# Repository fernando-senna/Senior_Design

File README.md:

# Senior_Design
Eye Tracker - Senior Design Project
As the name suggests this is a Systems Design project. Our goal is to design and develop an affordable, sleek and accurate eye tracking system. This project contains the entire documentation and code. 
                    # Last Updated: Oct 31, 2015

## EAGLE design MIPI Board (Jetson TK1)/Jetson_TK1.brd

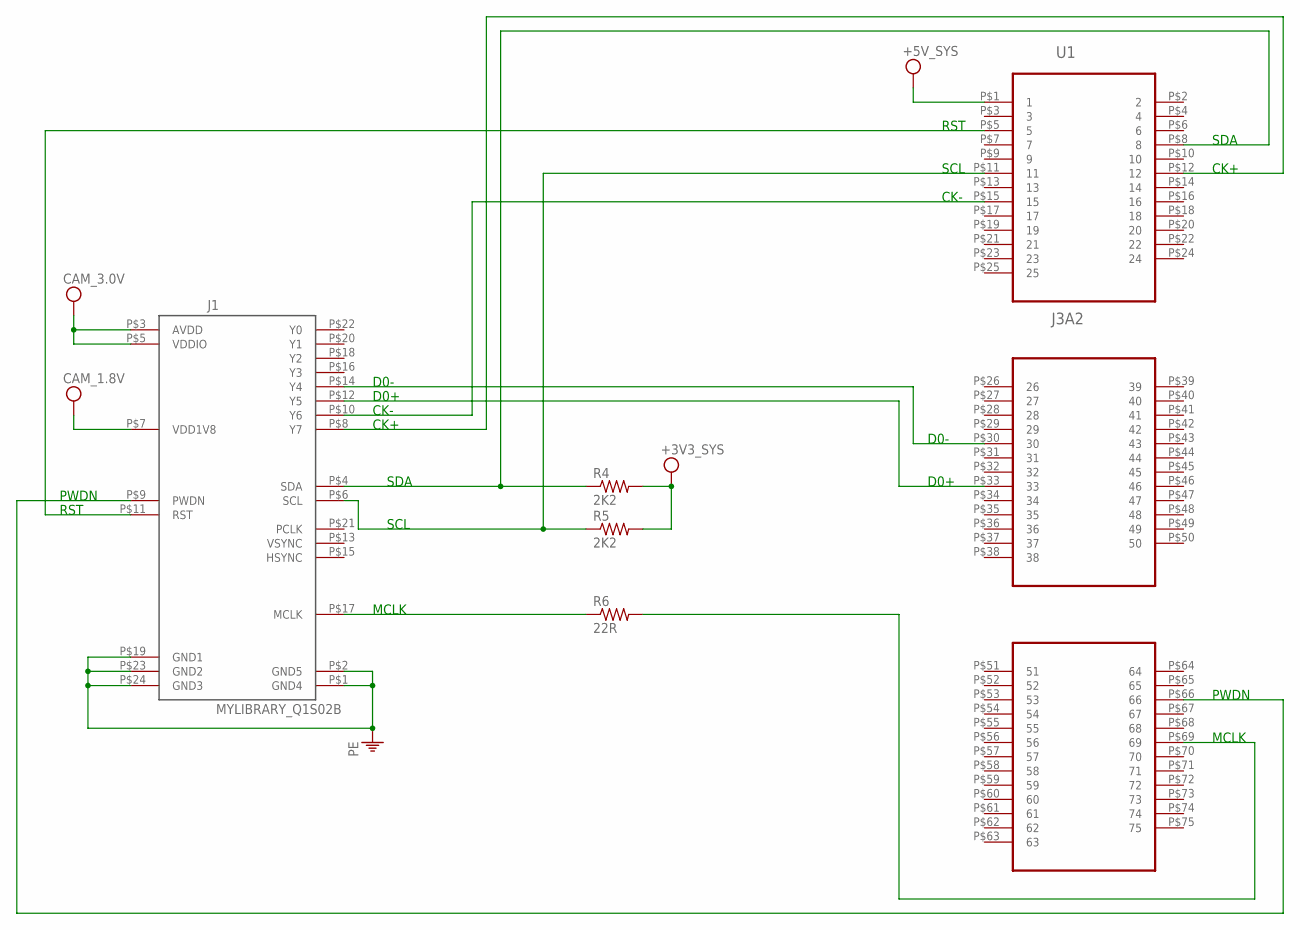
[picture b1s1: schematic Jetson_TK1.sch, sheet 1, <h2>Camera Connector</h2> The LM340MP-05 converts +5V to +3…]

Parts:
J1: MYLIBRARY_Q1S02B; MYLIBRARY_AXK824145WG
R4, R5: 2K2; R0603
R6: 22R; R0603
U1: J3A2; SQW-150-01-F-T

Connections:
unnamed: J1.P$8 (Y7), U1.P$12 (12)
unnamed: J1.P$4 (SDA), R4.1, U1.P$8 (8)
unnamed: J1.P$6 (SCL), R5.1, U1.P$11 (11)
unnamed: J1.P$10 (Y6), U1.P$15 (15)
unnamed: J1.P$12 (Y5), U1.P$33 (33)
unnamed: J1.P$14 (Y4), U1.P$30 (30)
unnamed: J1.P$17 (MCLK), R6.1
unnamed: R6.2, U1.P$69 (69)
unnamed: J1.P$11 (RST), U1.P$5 (5)
unnamed: J1.P$9 (PWDN), U1.P$66 (66)
PE: J1.P$1 (GND4), J1.P$2 (GND5), J1.P$19 (GND1), J1.P$23 (GND2), J1.P$24 (GND3); also elsewhere on the board
VDD: J1.P$3 (AVDD), J1.P$5 (VDDIO), J1.P$7 (VDD1V8), R4.2, R5.2, U1.P$1 (1); also elsewhere on the board

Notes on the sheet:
SDA
SCL
CK+
CK-
D0+
D0-
MCLK
RST
PWDN

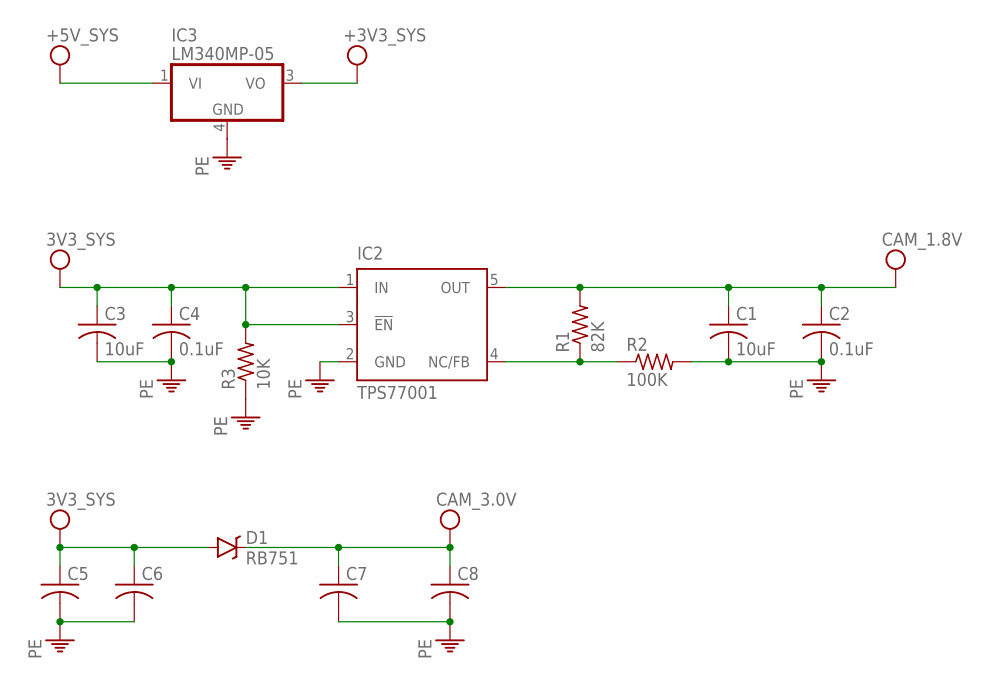
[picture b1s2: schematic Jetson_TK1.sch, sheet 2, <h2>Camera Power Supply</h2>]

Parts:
C1, C3: 10uF; C0603
C2, C4: 0.1uF; C0603
C5, C6, C7, C8: C-USC0603; C0603
D1: RB751; SOD-523
IC2: TPS77001; SOT23-DBV
IC3: LM340MP-05; SOT223
R1: 82K; R0603
R2: 100K; R0603
R3: 10K; R0603

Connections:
unnamed: IC2.4 (NC/FB), R1.1, R2.1
PE: C1.2, C2.2, C3.2, C4.2, C5.2, C6.2, C7.2, C8.2, IC2.2 (GND), IC3.4 (GND), R2.2, R3.1; also elsewhere on the board
VCC: C3.1, C4.1, C5.1, C6.1, D1.A, IC2.1 (IN), IC2.3 (!EN), IC3.1 (VI), IC3.3 (VO), R3.2
VDD: C1.1, C2.1, C7.1, C8.1, D1.C, IC2.5 (OUT), R1.2; also elsewhere on the board

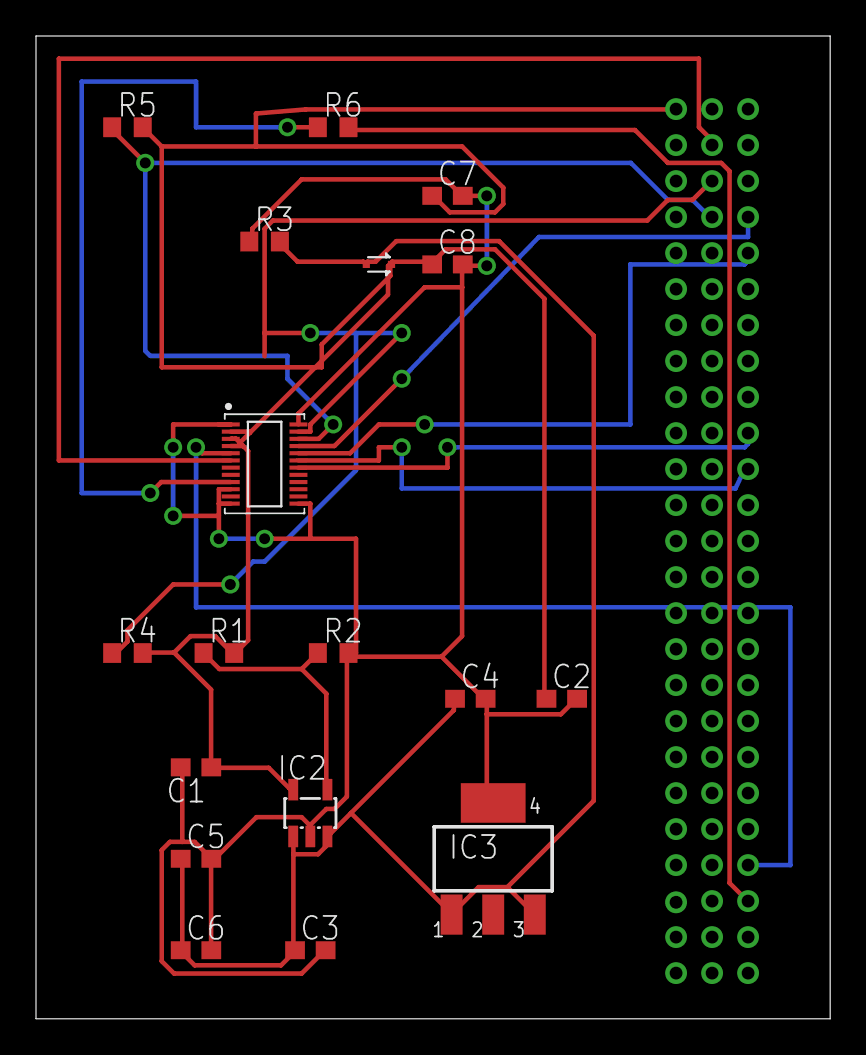
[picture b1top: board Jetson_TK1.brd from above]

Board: 2 copper layers, 44.1 x 54.6 mm, 19 parts (1 on the bottom side), 14 nets.

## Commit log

2015-10-07 Project Charter Latex
2015-10-07 [Completed Version 1 KM]
2015-10-28 [added requirements latex]
2015-10-28 [Updated tex files]
2015-10-28 Updated font size and Perception text
2015-10-28 edit header paragraph
2015-10-28 added header description
2015-10-28 added header paragraph
2015-10-28 Added Fernados Part
2015-10-28 Added
2015-10-28 edited header paragraph
2015-10-29 [First Draft Complete]
2015-11-01 [OpenCV Loading an Image]
2015-11-01 Deleted Zip
2015-11-04 [Professors eye tracker]
2015-11-04 Revert "[Professors eye tracker]"
    This reverts commit 9233dc499d4214e1dfbbbbb9bacde50000d56cb3.
2015-11-04 [Professor code]
2015-11-04 [Python Implementation]
2015-11-04 test file
2015-11-04 Testing
2015-11-04 Another test
2015-11-05 [Deleted test1.txt]
2015-11-05 [removed test2.txt]
2015-11-05 Deleted first opencv test file
2015-11-13 [Test files for opencv]
2015-11-16 compiled!
2015-11-18 [Added Architectural Specification]
2015-11-18 [Started Introduction]
2015-11-18 [Software 1st Draft Complete]
2015-11-25 [Updated Figures and Y and Z layers]
2015-11-25 Updated Layer Names & Output + Inputs (Interfaces)
2015-11-25 [Updated Fernandos Changes]
2015-12-07 [Added ransac]
2015-12-14 Testing
    making sure i've got the whole github thing down
2015-12-14 Removed that test file
2016-01-22 [Updated with Centroid working]
2016-01-25 [dynamic pupil center, size and angle]
2016-01-27 added cuda support
2016-01-29 [STARTED CUDA FYING JAN 29 ... Krishna Bhattarai]
2016-01-29 REmoved test cuda
2016-01-29 [JAN 29 GPU HISTOGRAM]
2016-01-30 [JAN 29 COMPUTER GPU CANNY]
2016-02-02 added connected component update to mcmurrough folder
2016-02-02 added paper authored by the pupil labs group (explains the tracker)
2016-02-03 Camera Board Schematic + PCB Design
2016-02-10 Updated BRD
2016-04-27 Website
2016-04-27 Update Everything

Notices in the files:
parts and their libraries:
SparkFun-DiscreteSemi: Licensing: Creative Commons ShareAlike 4.0 International - https://creativecommons.org/licenses/by-sa/4.0
